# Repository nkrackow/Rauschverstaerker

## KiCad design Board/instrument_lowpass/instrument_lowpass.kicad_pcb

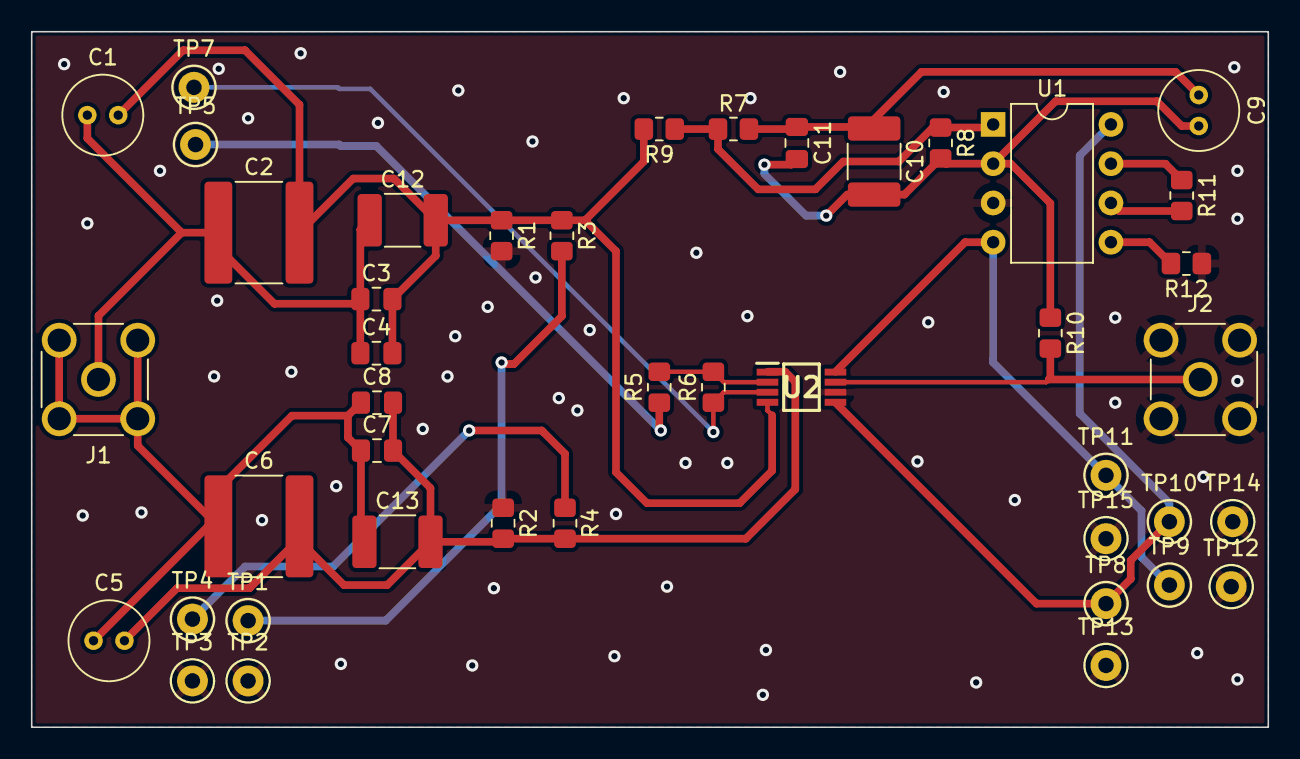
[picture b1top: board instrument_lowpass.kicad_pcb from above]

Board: 2 copper layers, 80.0 x 45.0 mm, 43 parts (0 on the bottom side), 19 nets.

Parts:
C1, C5, C9: C; C_Radial_D5.0mm_H5.0mm_P2.00mm
C2, C6: C; C_2225_5664Metric_Pad1.80x6.60mm_HandSolder
C3, C4, C7, C8, C11: C; C_0805_2012Metric_Pad1.18x1.45mm_HandSolder
C10, C12, C13: C; C_1812_4532Metric_Pad1.57x3.40mm_HandSolder
J1, J2: Conn_Coaxial; SMA_Molex_73251-2200_Horizontal
R1, R2, R3, R4, R5, R6, R7, R8, R9, R10, R11, R12: R; R_0805_2012Metric_Pad1.20x1.40mm_HandSolder
TP1: cutoff_signal+; TestPoint_Keystone_5000-5004_Miniature
TP2: cutoff_signal-; TestPoint_Keystone_5000-5004_Miniature
TP3: cutoff_reference-; TestPoint_Keystone_5000-5004_Miniature
TP4: cutoff_reference+; TestPoint_Keystone_5000-5004_Miniature
TP5: gain-; TestPoint_Keystone_5000-5004_Miniature
TP7: gain+; TestPoint_Keystone_5000-5004_Miniature
TP8, TP9, TP10, TP11, TP12, TP13, TP14, TP15: TP; TestPoint_Keystone_5000-5004_Miniature
U1: NJM2114; DIP-8_W7.62mm
U2: INA849DGKR; SOP65P490X110-8N

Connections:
+9V: TP8.1, TP10.1, U1.8 (V+), U2.5 (-VS)
-9V: TP9.1, TP11.1, U1.4 (V-), U2.8 (+VS)
/input: C1.1, C2.1, C3.1, C4.1, C12.1, J1.1 (In)
GND: J2.2 (Ext), R1.2, R2.1, R12.1, TP2.1, TP3.1, TP12.1, TP13.1, TP14.1, TP15.1, U1.3 (+), U2.6 (REF)
unnamed: C1.2, C2.2, C3.2, C4.2, C12.2, R1.1, R3.1, R9.2, U2.4 (+IN)
unnamed: C9.1, C10.1, C11.1, R7.2
unnamed: C9.2, C10.2, C11.2, R8.2, R10.1, U1.2 (-)
unnamed: C5.1, C6.1, C7.1, C8.1, C13.1, J1.2 (Ext)
unnamed: C5.2, C6.2, C7.2, C8.2, C13.2, R2.2, R4.2, U2.1 (-IN)
unnamed: J2.1 (In), R10.2, U2.7 (OUT)
unnamed: R3.2, TP1.1
unnamed: R4.1, TP4.1
unnamed: R5.1, TP5.1
unnamed: R5.2, R6.2, U2.2 (RG_1)
unnamed: R6.1, TP7.1, U2.3 (RG_2)
unnamed: R7.1, R8.1, R9.1, U1.1
unnamed: R11.1, U1.7
unnamed: R11.2, U1.6 (-)
unnamed: R12.2, U1.5 (+)

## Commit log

2023-10-31 add xcorr waveforms script experiments
2023-11-12 push changes
2023-11-12 add first schematic
2023-12-26 add schematic of instrumentation based approach. footprint assignment not done and layout not started
2023-12-26 finisched assignment and some layout
2024-01-06 add board design§
2024-01-06 move stuff on input side
2024-01-06 add final design and fab files
2024-01-13 add sim and the note about the fkin decimate sample mode..
